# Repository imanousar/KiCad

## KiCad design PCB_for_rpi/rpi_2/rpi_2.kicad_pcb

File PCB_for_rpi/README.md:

# PCB for Raspberry Pi 

A double-sided PCB for RaspberryPi made in KiCad.
It was built in the scope of a project in [R4A](https://r4a.issel.ee.auth.gr/).

<br>
<br>

<h3 align="center"> 3-D view of the PCB <h3>

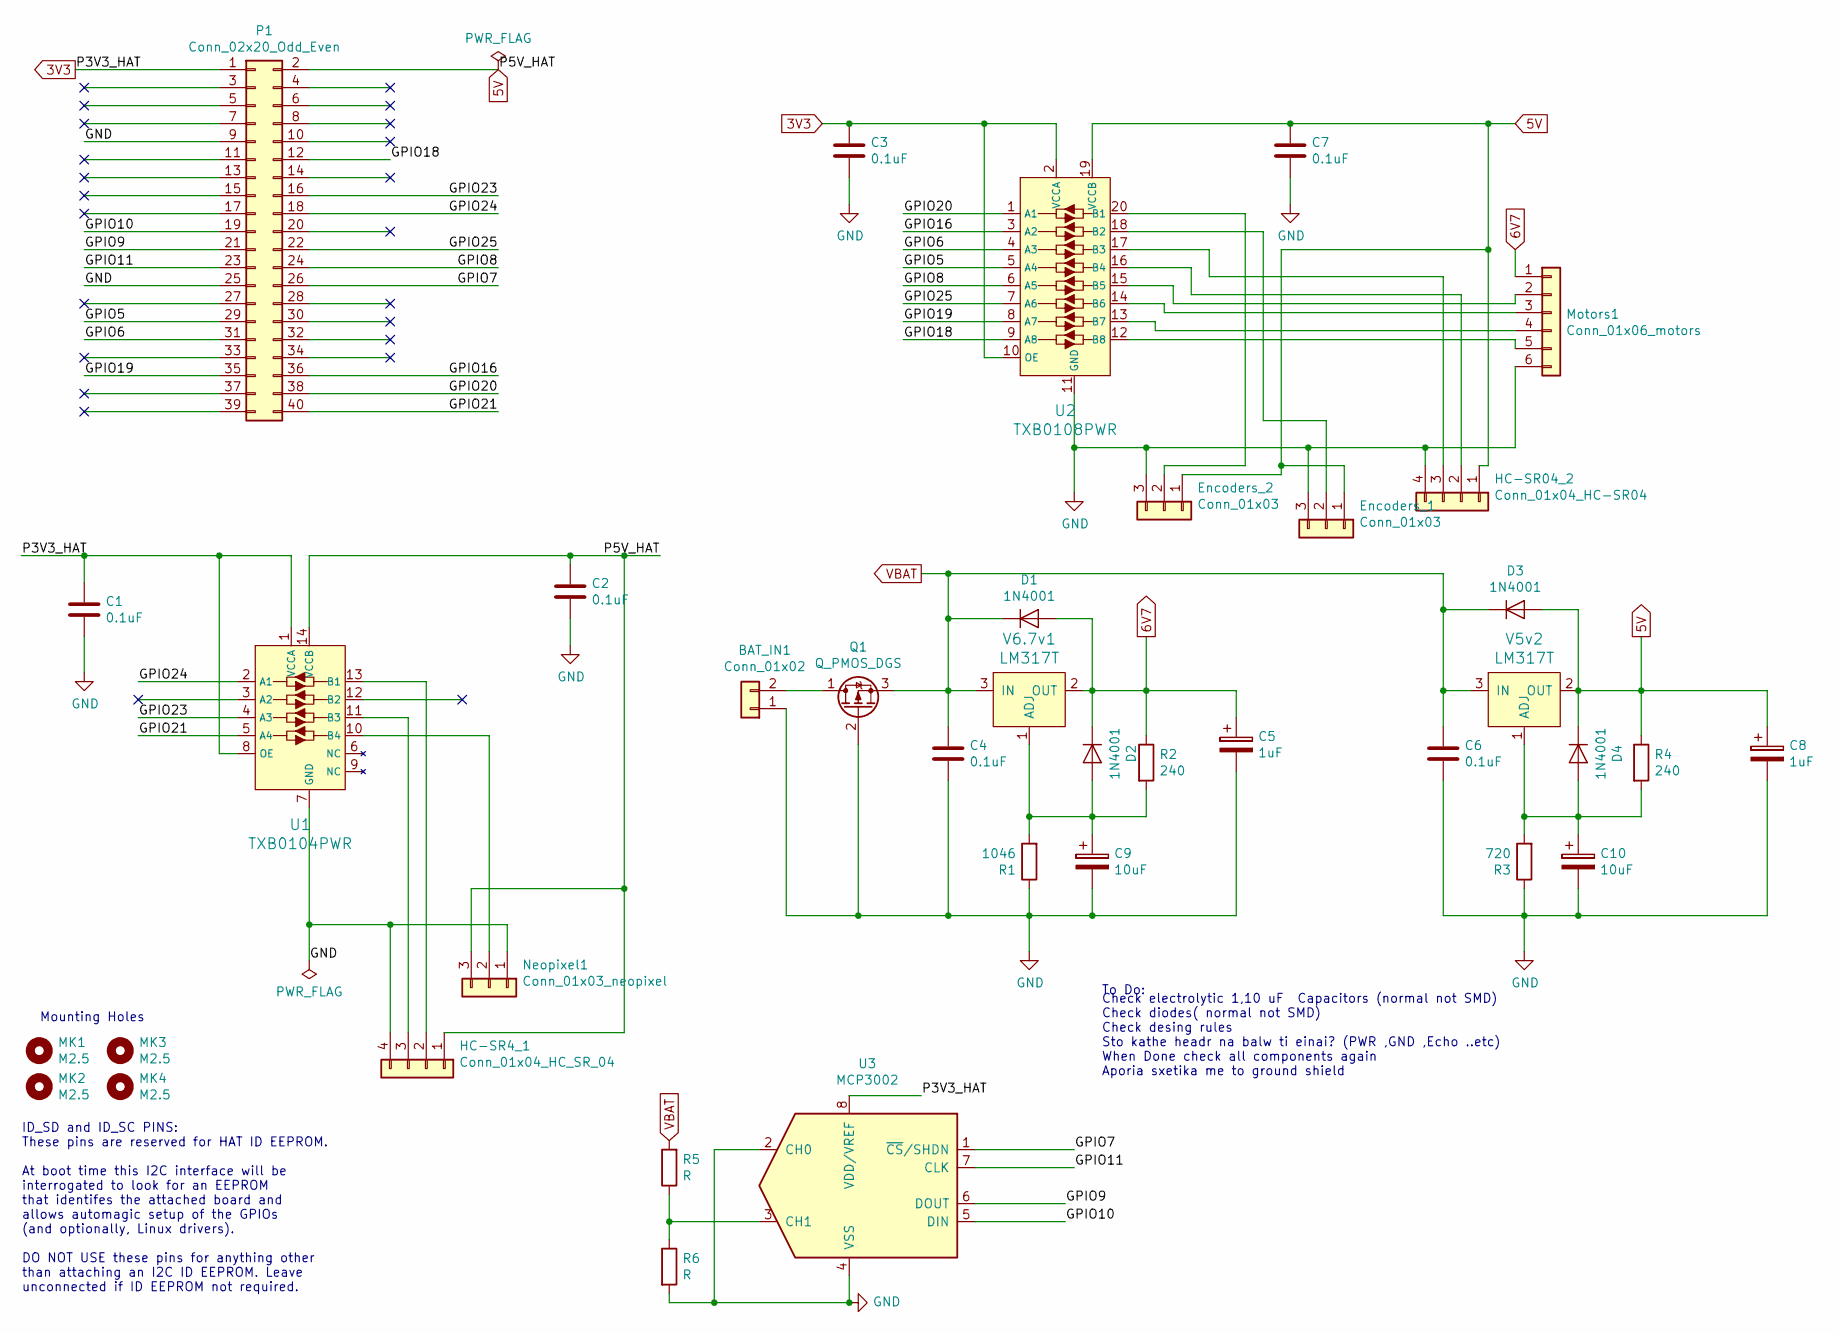
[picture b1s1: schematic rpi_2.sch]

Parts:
BAT_IN1: Conn_01x02; TerminalBlock_bornier-2_P5.08mm
C1, C2, C3, C4, C6, C7: 0.1uF; C_0805_2012Metric
C5, C8: 1uF; CP_Radial_D5.0mm_P2.00mm
C9, C10: 10uF; CP_Radial_D5.0mm_P2.00mm
D1, D2, D3, D4: 1N4001; D_DO-41_SOD81_P10.16mm_Horizontal
Encoders_1, Encoders_2: Conn_01x03; Molex_KK-254_AE-6410-03A_1x03_P2.54mm_Vertical
HC-SR4_1: Conn_01x04_HC_SR_04; Molex_KK-254_AE-6410-04A_1x04_P2.54mm_Vertical
HC-SR04_2: Conn_01x04_HC-SR04; Molex_KK-254_AE-6410-04A_1x04_P2.54mm_Vertical
MK1, MK2, MK3, MK4: M2.5; MountingHole_2.7mm_M2.5
Motors1: Conn_01x06_motors; Molex_KK-254_AE-6410-06A_1x06_P2.54mm_Vertical
Neopixel1: Conn_01x03_neopixel; Molex_KK-254_AE-6410-03A_1x03_P2.54mm_Vertical
P1: Conn_02x20_Odd_Even; PinSocket_2x20_P2.54mm_Vertical
Q1: Q_PMOS_DGS; SOT-23
R1: 1046; R_0805_2012Metric
R2, R4: 240; R_0805_2012Metric
R3: 720; R_0805_2012Metric
R5, R6: R; R_0805_2012Metric
U1: TXB0104PWR; SOIC-14_3.9x8.7mm_P1.27mm; MPN TXB0104PWR; Digi-Key_PN 296-21929-1-ND
U2: TXB0108PWR; TSSOP-20_4.4x6.5mm_P0.65mm; MPN TXB0108PWR; Digi-Key_PN 296-21527-1-ND
U3: MCP3002; TSSOP-8_4.4x3mm_P0.65mm
V5v2, V6.7v1: LM317T; TO-220-3_Vertical; MPN LM317T; Digi-Key_PN 497-1575-5-ND

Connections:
3V3: C1.1, C3.1, P1.1, U1.1 (VCCA), U1.8 (OE), U2.2 (VCCA), U2.10 (OE), U3.8 (VDD/VREF)
5V: C2.1, C7.1, C8.1, D3.2 (A), D4.1 (K), Encoders_1.1, Encoders_2.1, HC-SR4_1.1, HC-SR04_2.1, Neopixel1.3, P1.2, R4.1, U1.14 (VCCB), U2.19 (VCCB), V5v2.2 (OUT)
6V7: C5.1, D1.2 (A), D2.1 (K), Motors1.1, R2.1, V6.7v1.2 (OUT)
/GPIO5: P1.29, U2.5 (A4)
/GPIO6: P1.31, U2.4 (A3)
/GPIO7: P1.26, U3.1 (~CS~/SHDN)
/GPIO8: P1.24, U2.6 (A5)
/GPIO9: P1.21, U3.6 (DOUT)
/GPIO10: P1.19, U3.5 (DIN)
/GPIO11: P1.23, U3.7 (CLK)
/GPIO16: P1.36, U2.3 (A2)
/GPIO18: P1.12, U2.9 (A8)
/GPIO19: P1.35, U2.8 (A7)
/GPIO20: P1.38, U2.1 (A1)
/GPIO21: P1.40, U1.5 (A4)
/GPIO23: P1.16, U1.4 (A3)
/GPIO24: P1.18, U1.2 (A1)
/GPIO25: P1.22, U2.7 (A6)
GND: BAT_IN1.1, C1.2, C2.2, C3.2, C4.2, C5.2, C6.2, C7.2, C8.2, C9.2, C10.2, Encoders_1.3, Encoders_2.3, HC-SR4_1.4, HC-SR04_2.4, Motors1.6, Neopixel1.1, P1.9, P1.25, Q1.2 (G), R1.1, R3.1, R6.2, U1.7 (GND), U2.11 (GND), U3.2 (CH0), U3.4 (VSS)
unnamed: BAT_IN1.2, Q1.1 (D)
unnamed: C9.1, D2.2 (A), R1.2, R2.2, V6.7v1.1 (ADJ)
unnamed: C10.1, D4.2 (A), R3.2, R4.2, V5v2.1 (ADJ)
unnamed: Encoders_1.2, U2.18 (B2)
unnamed: Encoders_2.2, U2.20 (B1)
unnamed: HC-SR4_1.2, U1.13 (B1)
unnamed: HC-SR4_1.3, U1.11 (B3)
unnamed: HC-SR04_2.2, U2.16 (B4)
unnamed: HC-SR04_2.3, U2.17 (B3)
unnamed: Motors1.2, U2.15 (B5)
unnamed: Motors1.3, U2.14 (B6)
unnamed: Motors1.4, U2.13 (B7)
unnamed: Motors1.5, U2.12 (B8)
unnamed: Neopixel1.2, U1.10 (B4)
unnamed: R5.1, R6.1, U3.3 (CH1)
VBAT: C4.1, C6.1, D1.1 (K), D3.1 (K), Q1.3 (S), R5.2, V5v2.3 (IN), V6.7v1.3 (IN)

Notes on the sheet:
ID_SD and ID_SC PINS: These pins are reserved for HAT ID EEPROM. At boot time this I2C interface will be interrogated to look for an EEPROM that identifes the attached board and allows automagic setup of the GPIOs (and optionally, Linux drivers). DO NOT USE these pins for anything other than attach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
Mounting Holes
Check electrolytic 1,10 uF Capacitors (normal not SMD) Check diodes( normal not SMD) Check desing rules Sto kathe headr na balw ti einai? (PWR ,GND ,Echo ..etc) When Done check all components again Aporia sxetika me to ground shield
To Do:

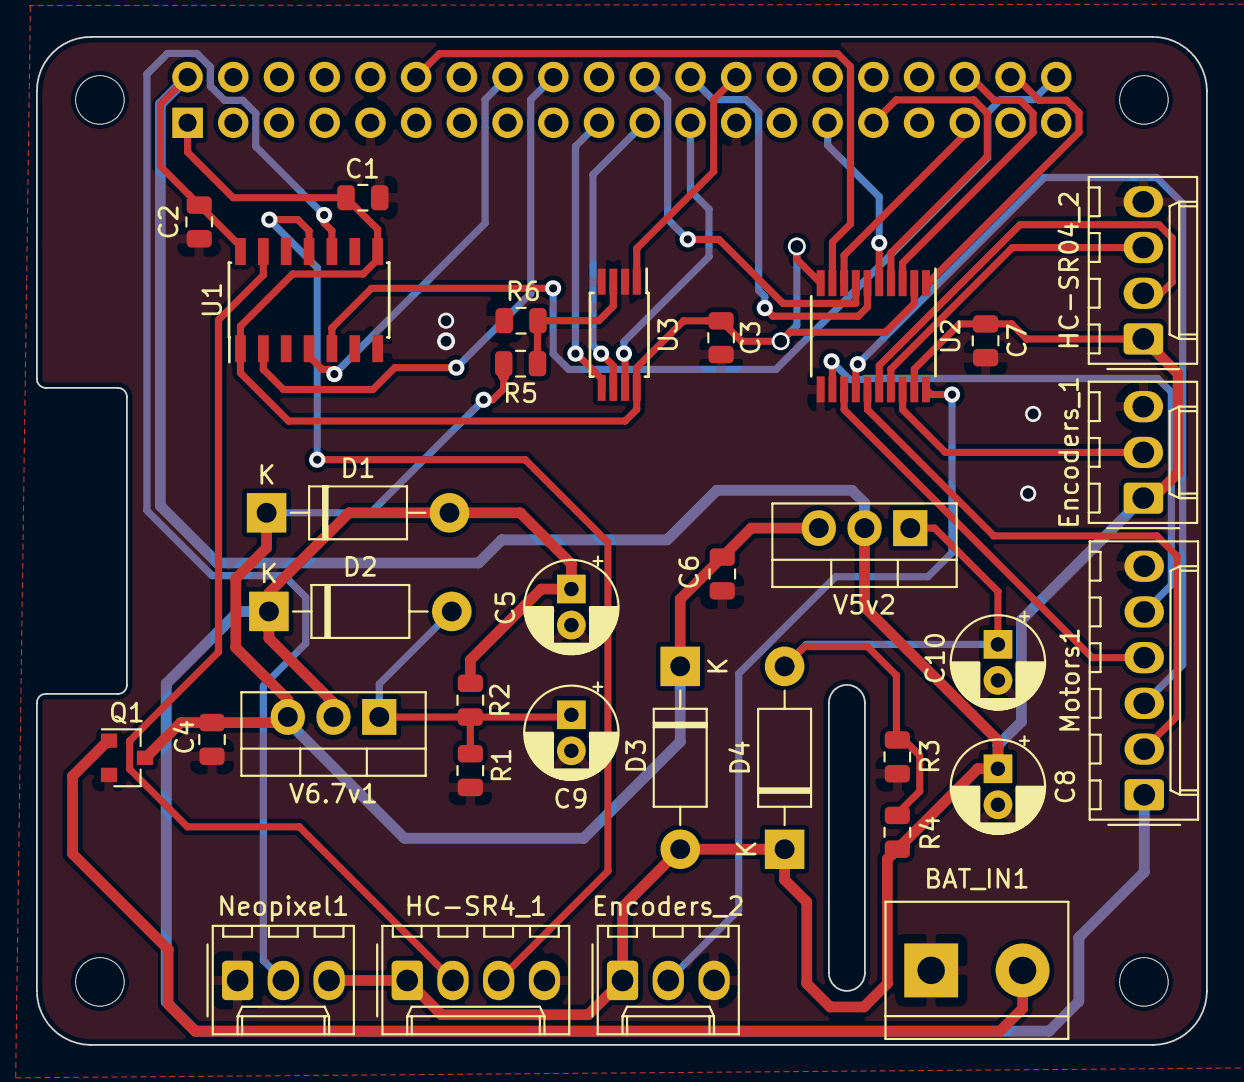
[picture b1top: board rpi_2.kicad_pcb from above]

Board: 2 copper layers, 65.0 x 56.0 mm, 38 parts (1 on the bottom side), 35 nets.
